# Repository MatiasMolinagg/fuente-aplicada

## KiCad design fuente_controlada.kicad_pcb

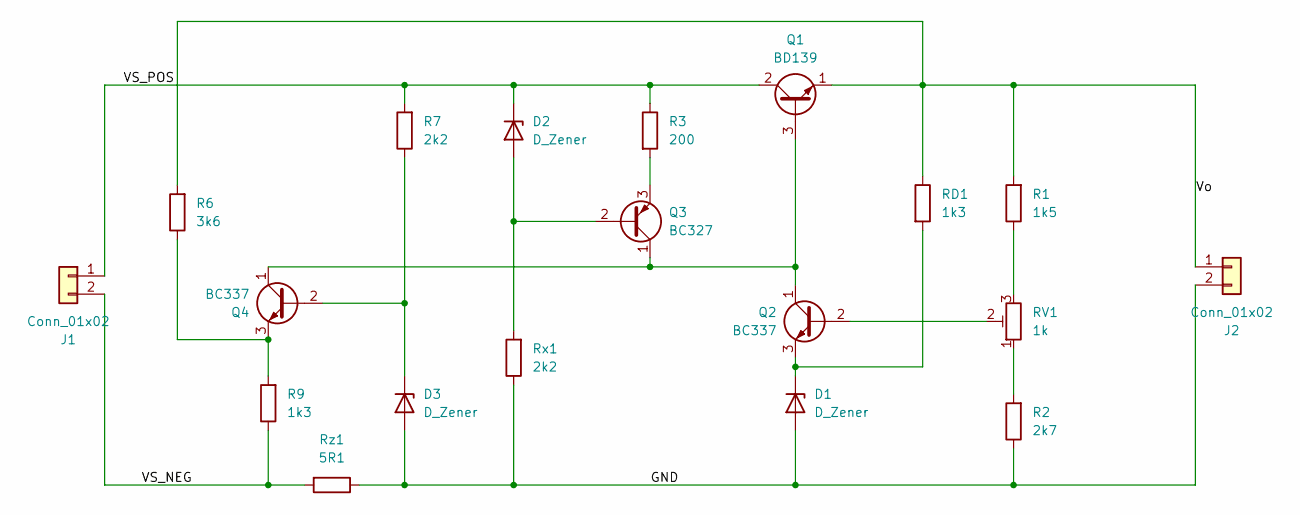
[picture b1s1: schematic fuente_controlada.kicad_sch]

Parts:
D1: D_Zener; D_DO-41_SOD81_P10.16mm_Horizontal
D2, D3: D_Zener; D_DO-35_SOD27_P7.62mm_Horizontal
J1, J2: Conn_01x02; PinHeader_1x02_P2.54mm_Vertical
Q1: BD139; TO-126-3_Vertical
Q2, Q4: BC337; TO-92_Inline_Wide
Q3: BC327; TO-92_Inline_Wide
R1: 1k5; R_Axial_DIN0207_L6.3mm_D2.5mm_P10.16mm_Horizontal
R2: 2k7; R_Axial_DIN0207_L6.3mm_D2.5mm_P10.16mm_Horizontal
R3: 200; R_Axial_DIN0207_L6.3mm_D2.5mm_P10.16mm_Horizontal
R6: 3k6; R_Axial_DIN0207_L6.3mm_D2.5mm_P10.16mm_Horizontal
R7: 2k2; R_Axial_DIN0207_L6.3mm_D2.5mm_P10.16mm_Horizontal
R9: 1k3; R_Axial_DIN0207_L6.3mm_D2.5mm_P10.16mm_Horizontal
RD1: 1k3; R_Axial_DIN0207_L6.3mm_D2.5mm_P10.16mm_Horizontal
RV1: 1k; Potentiometer_Bourns_3296W_Vertical
Rx1: 2k2; R_Axial_DIN0207_L6.3mm_D2.5mm_P10.16mm_Horizontal
Rz1: 5R1; R_Axial_DIN0207_L6.3mm_D2.5mm_P10.16mm_Horizontal

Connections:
/GND: D1.2 (A), D3.2 (A), J2.2, R2.1, Rx1.1, Rz1.1
/VS_NEG: J1.2, R9.1, Rz1.2
/VS_POS: D2.1 (K), J1.1, Q1.2 (C), R3.1, R7.2
/Vo: J2.1, Q1.1 (E), R1.2, R6.2, RD1.1
unnamed: D1.1 (K), Q2.3 (E), RD1.2
unnamed: D2.2 (A), Q3.2 (B), Rx1.2
unnamed: D3.1 (K), Q4.2 (B), R7.1
unnamed: Q1.3 (B), Q2.1 (C), Q3.1 (C), Q4.1 (C)
unnamed: Q2.2 (B), RV1.2
unnamed: Q3.3 (E), R3.2
unnamed: Q4.3 (E), R6.1, R9.2
unnamed: R1.1, RV1.3
unnamed: R2.2, RV1.1

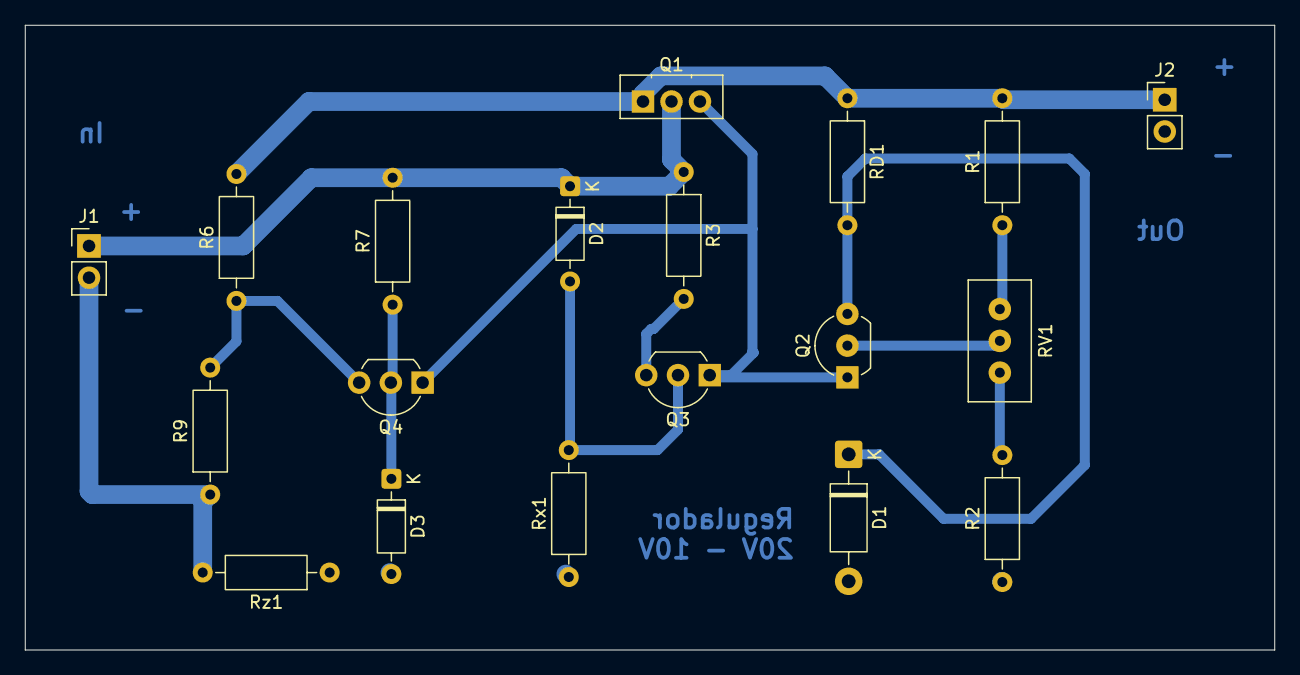
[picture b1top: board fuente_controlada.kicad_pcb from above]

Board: 2 copper layers, 100.0 x 50.0 mm, 19 parts (0 on the bottom side), 13 nets.
